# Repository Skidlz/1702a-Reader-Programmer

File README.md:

# 1702a Reader and Programmer
A DIY, arduino-based 1702a Reader and Programmer

Included are Eagle CAD schematics + board layouts, and Arduino source code

[Blog post](https://zeninstruments.blogspot.com/2020/06/diy-1702a-programmer.html)

Prommer Schematic

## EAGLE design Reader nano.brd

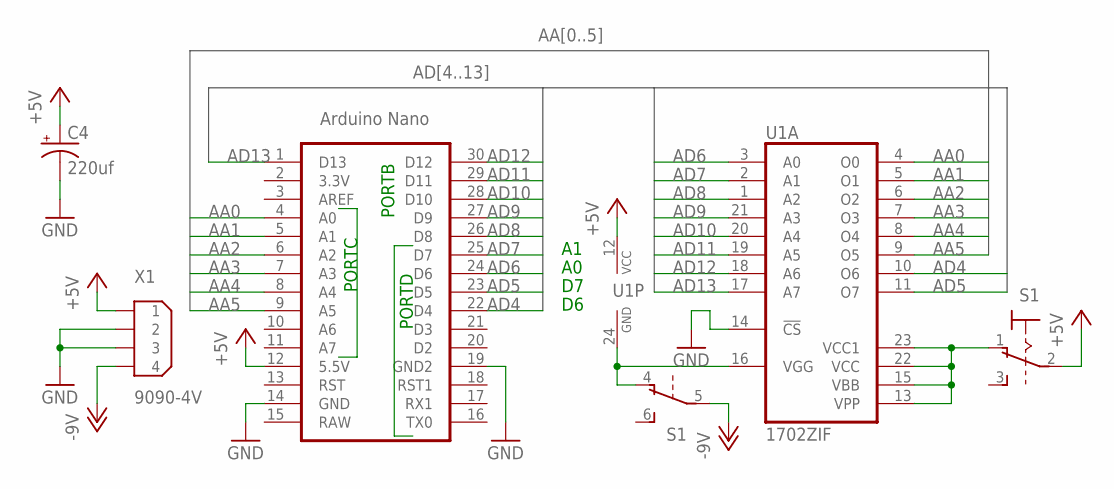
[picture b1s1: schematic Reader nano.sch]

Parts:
C4: 220uf; E5-10,5
S1: 320-938
U1: 1702ZIF; ZIF24
U$1: NANO
X1: 9090-4V

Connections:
+5V: C4.+, S1.2, U1.12 (VCC), U$1.12 (5.5V), X1.1
-12V: S1.5, X1.4
AA0: U1.4 (O0), U$1.4 (A0)
AA1: U1.5 (O1), U$1.5 (A1)
AA2: U1.6 (O2), U$1.6 (A2)
AA3: U1.7 (O3), U$1.7 (A3)
AA4: U1.8 (O4), U$1.8 (A4)
AA5: U1.9 (O5), U$1.9 (A5)
AD4: U1.10 (O6), U$1.22 (D4)
AD5: U1.11 (O7), U$1.23 (D5)
AD6: U1.3 (A0), U$1.24 (D6)
AD7: U1.2 (A1), U$1.25 (D7)
AD8: U1.1 (A2), U$1.26 (D8)
AD9: U1.21 (A3), U$1.27 (D9)
AD10: U1.20 (A4), U$1.28 (D10)
AD11: U1.19 (A5), U$1.29 (D11)
AD12: U1.18 (A6), U$1.30 (D12)
AD13: U1.17 (A7), U$1.1 (D13)
GND: C4.-, U1.14 (!CS), U$1.14 (GND), U$1.19 (GND2), X1.2, X1.3
unnamed: S1.1 (O), U1.13 (VPP), U1.15 (VBB), U1.22 (VCC), U1.23 (VCC1)
unnamed: S1.4 (O), U1.16 (VGG), U1.24 (GND)

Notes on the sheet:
PORTC
PORTD
PORTB

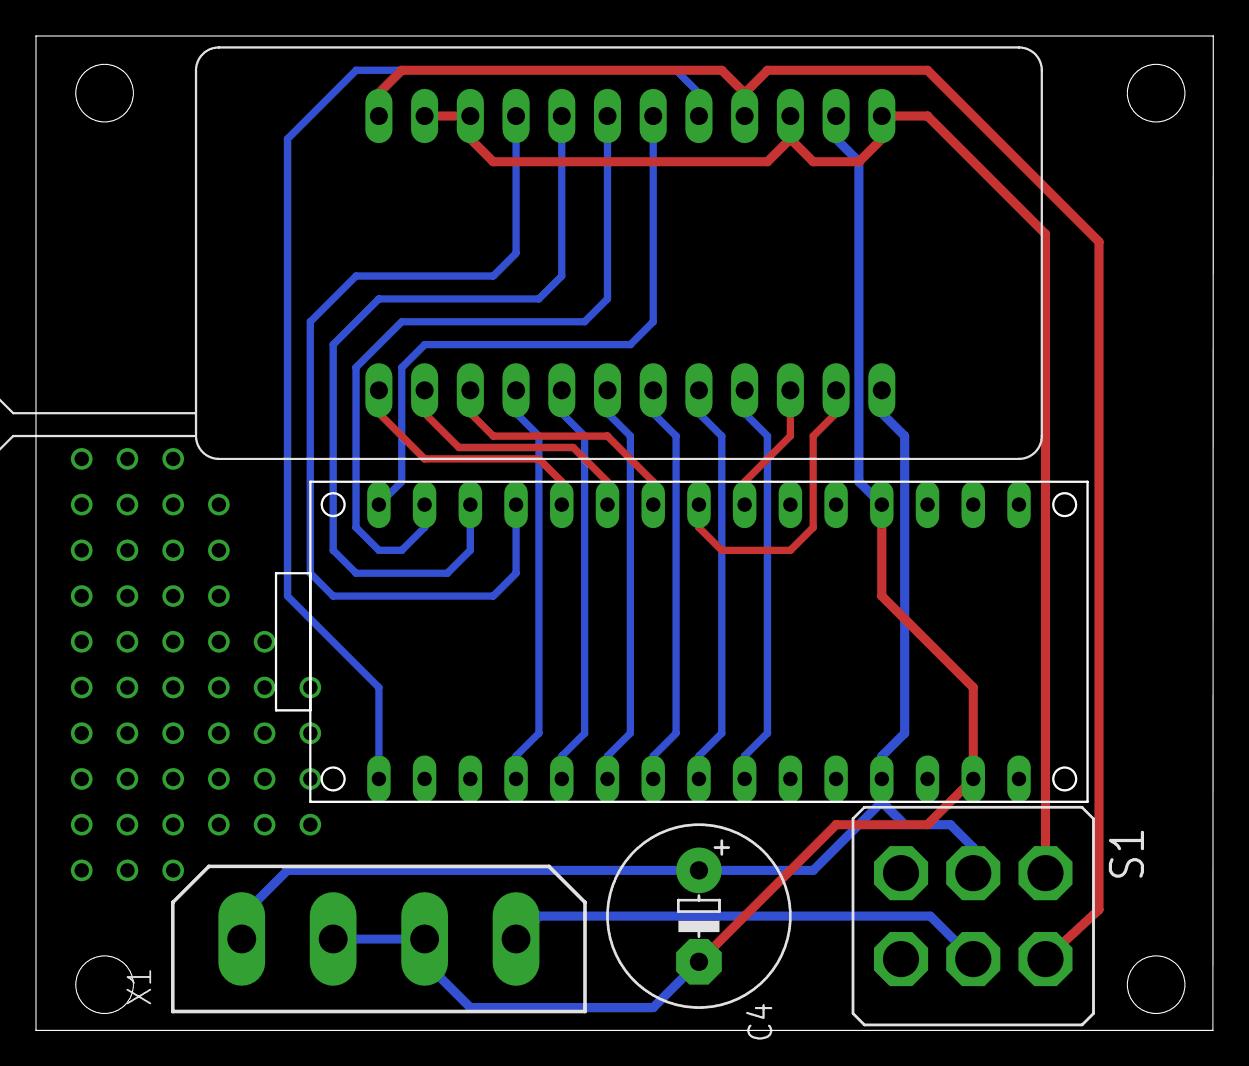
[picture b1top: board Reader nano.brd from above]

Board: 2 copper layers, 65.3 x 55.1 mm, 5 parts (0 on the bottom side), 21 nets.

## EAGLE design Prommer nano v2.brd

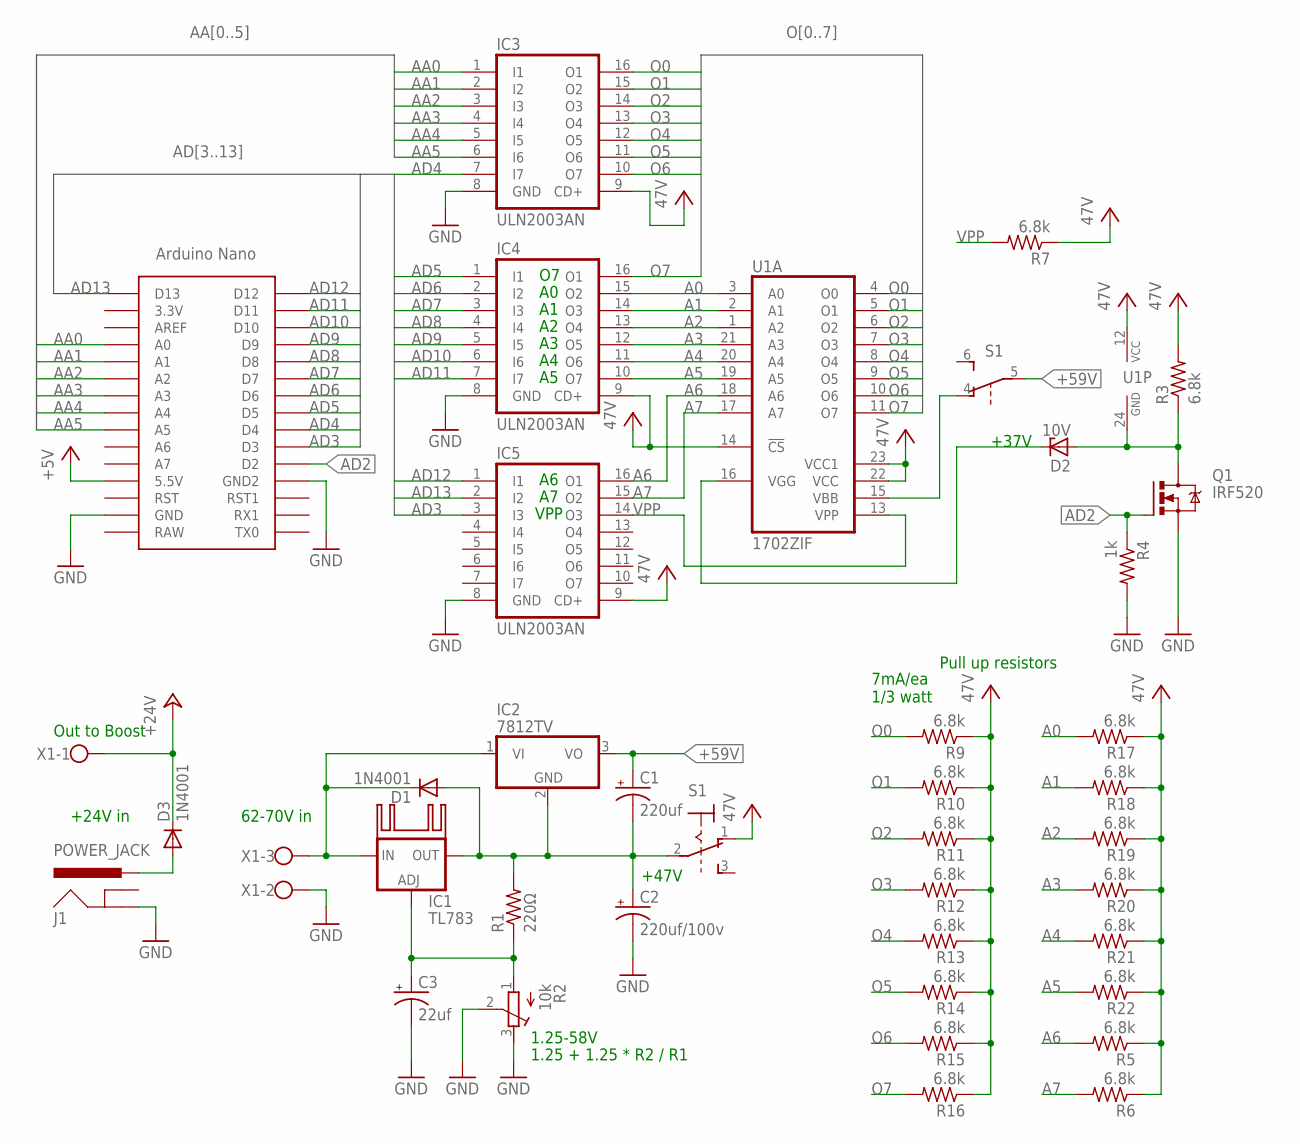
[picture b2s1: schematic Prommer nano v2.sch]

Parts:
C1: 220uf; E5-10,5
C2: 220uf/100v; E5-13
C3: 22uf; E5-10,5
D1, D3: 1N4001; D-7.5
D2: 10V; DO34Z7
IC1: TL783; 317TS
IC2: 7812TV; TO220V
IC3, IC4, IC5: ULN2003AN; DIL16
J1: POWER_JACK; POWER_JACK_PTH
KK1: SK95-2M3
Q1: IRF520; TO220BV
R1: 220Ω; 0207/10
R2: 10k; RTRIM64W
R3, R5, R6, R7, R9, R10, R11, R12, R13, R14, R15, R16, R17, R18, R19, R20, R21, R22: 6.8k; 0207/10
R4: 1k; 0207/10
S1: 320-938
U1: 1702ZIF; ZIF24
U$1: NANO
X1: W237-103

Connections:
+5V: U$1.5V (5.5V)
+24V: D3.C, X1.1
+47V: IC3.9 (CD+), IC4.9 (CD+), IC5.9 (CD+), R3.2, R5.1, R6.1, R7.1, R9.1, R10.1, R11.1, R12.1, R13.1, R14.1, R15.1, R16.1, R17.1, R18.1, R19.1, R20.1, R21.1, R22.1, S1.1 (O), U1.12 (VCC), U1.14 (!CS), U1.22 (VCC), U1.23 (VCC1)
+59V: C1.+, IC2.3 (VO), S1.5
A0: IC4.15 (O2), R17.2, U1.3 (A0)
A1: IC4.14 (O3), R18.2, U1.2 (A1)
A2: IC4.13 (O4), R19.2, U1.1 (A2)
A3: IC4.12 (O5), R20.2, U1.21 (A3)
A4: IC4.11 (O6), R21.2, U1.20 (A4)
A5: IC4.10 (O7), R22.2, U1.19 (A5)
A6: IC5.16 (O1), R5.2, U1.18 (A6)
A7: IC5.15 (O2), R6.2, U1.17 (A7)
AA0: IC3.1 (I1), U$1.A0
AA1: IC3.2 (I2), U$1.A1
AA2: IC3.3 (I3), U$1.A2
AA3: IC3.4 (I4), U$1.A3
AA4: IC3.5 (I5), U$1.A4
AA5: IC3.6 (I6), U$1.A5
AD2: Q1.G, R4.1, U$1.D2
AD3: IC5.3 (I3), U$1.D3
AD4: IC3.7 (I7), U$1.D4
AD5: IC4.1 (I1), U$1.D5
AD6: IC4.2 (I2), U$1.D6
AD7: IC4.3 (I3), U$1.D7
AD8: IC4.4 (I4), U$1.D8
AD9: IC4.5 (I5), U$1.D9
AD10: IC4.6 (I6), U$1.D10
AD11: IC4.7 (I7), U$1.D11
AD12: IC5.1 (I1), U$1.D12
AD13: IC5.2 (I2), U$1.D13
GND: C2.-, C3.-, IC3.8 (GND), IC4.8 (GND), IC5.8 (GND), J1.GND, Q1.S, R2.2 (S), R2.3 (E), R4.2, U$1.GND, U$1.GND1 (GND2), X1.2
unnamed: D1.C, IC1.3 (IN), IC2.1 (VI), X1.3
unnamed: C3.+, IC1.1 (ADJ), R1.1, R2.1 (A)
unnamed: D2.C, U1.16 (VGG)
unnamed: D2.A, Q1.D, R3.1, U1.24 (GND)
unnamed: C1.-, C2.+, D1.A, IC1.2 (OUT), IC2.2 (GND), R1.2, S1.2
unnamed: D3.A, J1.PWR
unnamed: S1.4 (O), U1.15 (VBB)
O0: IC3.16 (O1), R9.2, U1.4 (O0)
O1: IC3.15 (O2), R10.2, U1.5 (O1)
O2: IC3.14 (O3), R11.2, U1.6 (O2)
O3: IC3.13 (O4), R12.2, U1.7 (O3)
O4: IC3.12 (O5), R13.2, U1.8 (O4)
O5: IC3.11 (O6), R14.2, U1.9 (O5)
O6: IC3.10 (O7), R15.2, U1.10 (O6)
O7: IC4.16 (O1), R16.2, U1.11 (O7)
VPP: IC5.14 (O3), R7.2, U1.13 (VPP)

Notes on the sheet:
62-70V in
+47V
1.25-58V
1.25 + 1.25 * R2 / R1
+24V in
Out to Boost
VPP
Pull up resistors
7mA/ea 1/3 watt
+37V

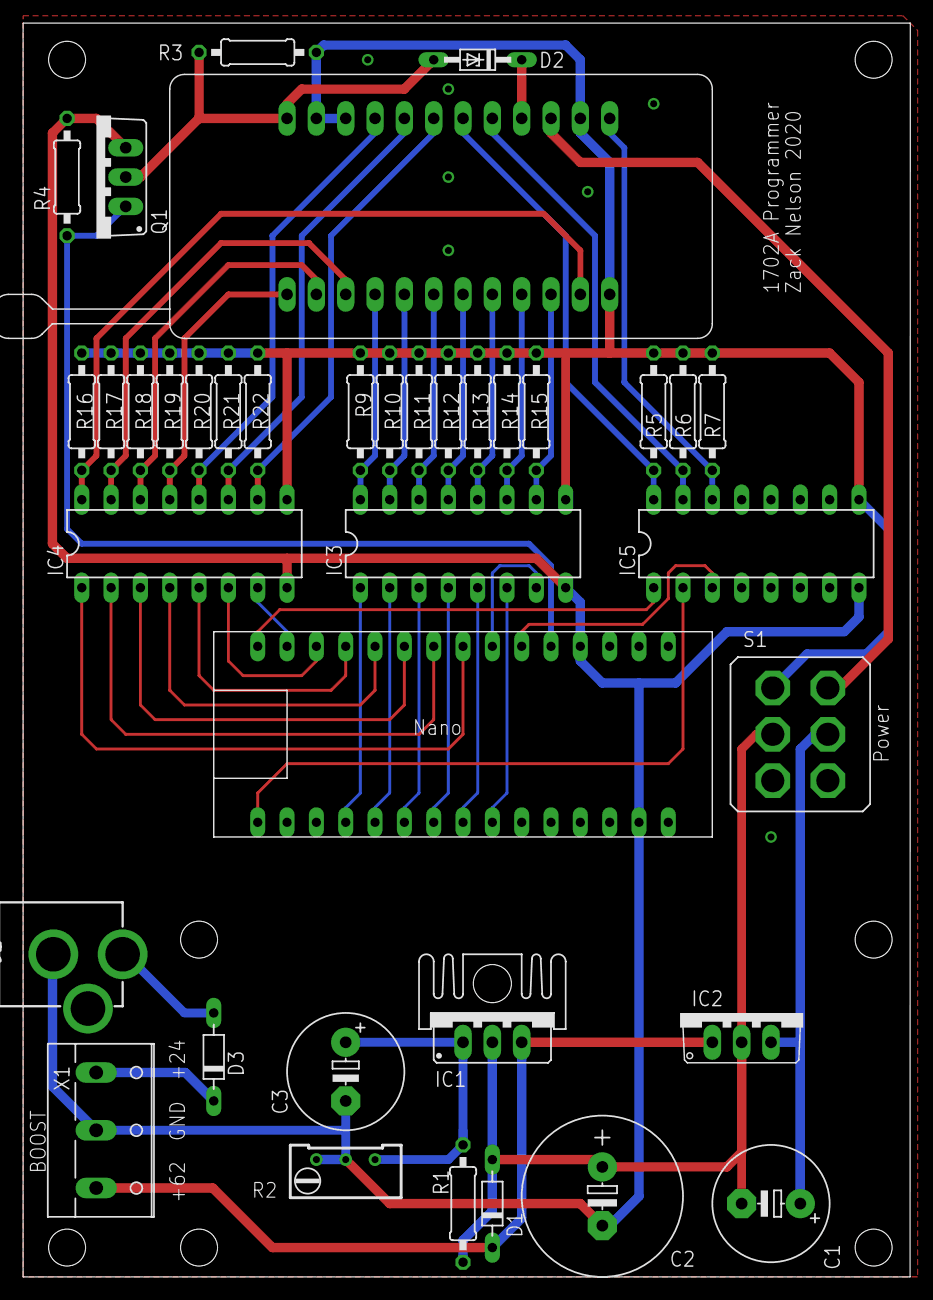
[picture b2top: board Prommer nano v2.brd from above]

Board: 2 copper layers, 76.8 x 108.6 mm, 39 parts (0 on the bottom side), 46 nets.

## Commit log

2022-12-03 Init
2022-12-03 Adding images

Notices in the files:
parts and their libraries:
SparkFun-Connectors: Licensing: Creative Commons ShareAlike 4.0 International - https://creativecommons.org/licenses/by-sa/4.0
